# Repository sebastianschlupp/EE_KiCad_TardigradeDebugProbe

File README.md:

# Revision 0.1

## Hardware Design Description

## Test Results

✅ Voltage outputs OK: VUSB and 1V8

✅ SWD interface OK: connected and successfully erased using J-Link Segger and J-Flash Lite

✅ LEDs OK: VBUS; DBG_LED0; DBG_LED1; VCC; TGT_RESET (remark TGT_RESET led is on when reset is high so inactive ... might want to consider inverting LED in the future)

❌ USB interface not working at 1.8V: please see SAMD21 datasheet chapter 37.15: "The operating voltages must be 3.3V (Min. 3.0V, Max. 3.6V)."

✅ USB interface working at 3.3V

✅ Flashing using west and pyOCD working

## Planned Design Changes

- Replace LT1962-1.8 with a 3.3V regulator. Also look for a cheaper option since the LT part is around 5€
- Check BOM and investigate need for alternatives (optimise for availability and price)

---

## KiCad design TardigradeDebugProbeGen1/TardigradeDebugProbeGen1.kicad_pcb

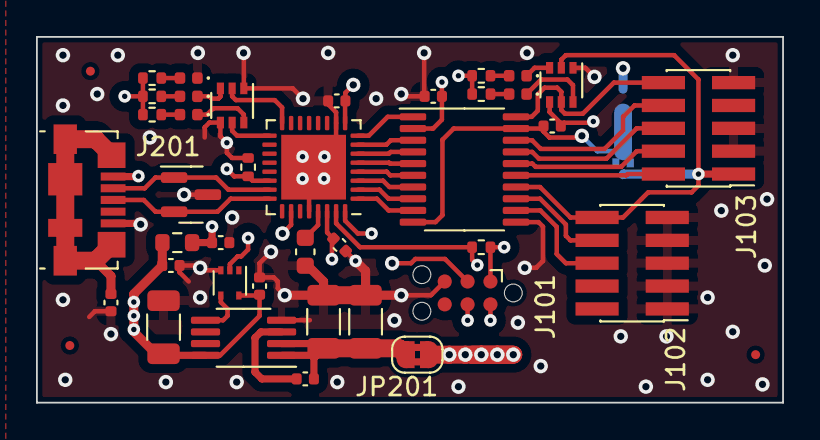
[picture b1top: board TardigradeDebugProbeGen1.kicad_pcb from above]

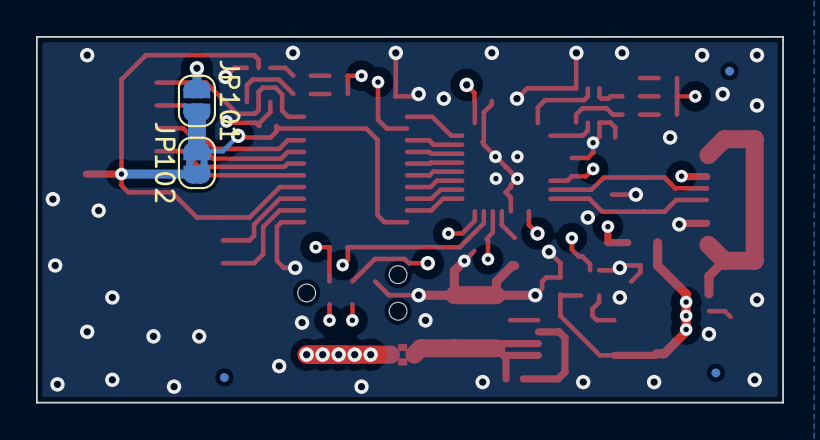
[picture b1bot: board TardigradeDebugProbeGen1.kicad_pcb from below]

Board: 6 copper layers, 41.5 x 20.3 mm, 46 parts (5 on the bottom side), 43 nets.

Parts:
C101, C102, C104, C105, C202, C203, C204: 100nF; C_0402_1005Metric
C103: 1uF; C_0603_1608Metric
C201: 4.7nF; C_0402_1005Metric
C205, C207, C208: 10uF; C_1206_3216Metric
C206: 10nF; C_0402_1005Metric
D101, D102: YELLOW; LED_0402_1005Metric
D103: RED; LED_0402_1005Metric
D104: GREEN; LED_0402_1005Metric
D201: LED; LED_0402_1005Metric
D202: SP0502BAHT; SOT-23
FB201: FerriteBead; R_0603_1608Metric
FID1, FID2, FID3, FID4, FID5, FID6: Fiducial; Fiducial_0.5mm_Mask1mm
J101: Conn_ARM_SWD_TagConnect_TC2030-NL; Tag-Connect_TC2030-IDC-NL_2x03_P1.27mm_Vertical
J102: Conn_02x05_Odd_Even; PinHeader_2x05_P1.27mm_Vertical_SMD
J103: Conn_ARM_JTAG_SWD_10; PinHeader_2x05_P1.27mm_Vertical_SMD
J201: USB_B_Micro; USB_Micro-B_Molex_47346-0001
JP101: SolderJumper_2_Open; SolderJumper-2_P1.3mm_Open_RoundedPad1.0x1.5mm
JP102, JP201: SolderJumper_2_Bridged; SolderJumper-2_P1.3mm_Bridged2Bar_RoundedPad1.0x1.5mm
Q101, Q102: ADC114; SOT-363_SC-70-6
R101, R102: 1k; R_0402_1005Metric
R103, R104, R105: 150; R_0402_1005Metric
R106, R201: 470; R_0402_1005Metric
U101: ATSAMD21E18A-M; QFN-32-1EP_5x5mm_P0.5mm_EP3.6x3.6mm
U102: TXS0108EPW; TSSOP-20_4.4x6.5mm_P0.65mm
U202: SN74LVC1G14DRL; SOT-553
U203: LT1962-1.8; MSOP-8_3x3mm_P0.65mm

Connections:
+1V8: C101.1, C102.1, C104.1, J101.1 (VCC), JP101.1 (A), JP201.2 (B), R101.2, U101.9 (VDDANA), U101.30 (VDDIN), U102.2 (VCCA)
/DBG_LED0: Q101.2 (B1), U101.16 (PA15)
/DBG_LED1: Q101.5 (B2), U101.17 (PA16)
/DBG_UART_RXD: J102.8, U102.13 (B7)
/DBG_UART_TXD: J102.6, U102.12 (B8)
/MCU_HARAKIRI: R102.2, U101.22 (PA23), U202.2
/SERCOM0_PAD1_SWO: U101.6 (PA05), U102.4 (A3)
/SERCOM1_PAD0_UART_TXD: U101.1 (PA00), U102.9 (A8)
/SERCOM1_PAD1_UART_RXD: U101.2 (PA01), U102.8 (A7)
/USB/USB_D+: D202.2 (K), J201.3 (D+), U101.24 (PA25)
/USB/USB_D-: D202.1 (K), J201.2 (D-), U101.23 (PA24)
GNDREF: C101.2, C102.2, C103.2, C104.2, C105.2, C201.1, C202.2, C203.2, C204.2, C205.2, C207.2, C208.2, D201.1 (K), D202.3 (A), J101.5 (GND), J102.1, J102.3, J102.5, J102.7, J102.9, J103.3 (GND), J103.5 (GND), J103.9 (GNDDetect), J201.5 (GND), Q101.1 (E1), Q101.4 (E2), Q102.1 (E1), Q102.4 (E2), R102.1, U101.10 (GND), U101.28 (GND), U101.33 (EP), U102.11 (GND), U202.3 (GND), U203.4 (GND)
unnamed: D101.2 (A), R103.1
unnamed: D101.1 (K), Q101.6 (C1)
unnamed: D102.2 (A), R104.1
unnamed: D102.1 (K), Q101.3 (C2)
unnamed: D103.2 (A), R105.1
unnamed: D103.1 (K), Q102.3 (C2)
unnamed: D104.2 (A), R106.1
unnamed: D104.1 (K), Q102.6 (C1)
unnamed: D201.2 (A), R201.1
unnamed: J101.4 (SWCLK), R101.1, U101.31 (PA30)
unnamed: J101.2 (SWDIO), U101.32 (PA31)
unnamed: J101.3 (~RESET), U101.26 (~RESET)
unnamed: J103.8 (NC/TDI), U102.18 (B2)
unnamed: J103.4 (SWDCLK/TCK), U102.16 (B4)
unnamed: J103.2 (SWDIO/TMS), U102.15 (B5)
unnamed: J103.6 (SWO/TDO), U102.17 (B3)
unnamed: C201.2, J201.6 (Shield)
unnamed: C203.1, FB201.1, J201.1 (VBUS)
unnamed: C105.1, JP101.2 (B), JP102.2 (B), U102.10 (OE), U102.19 (VCCB)
unnamed: C206.2, C207.1, C208.1, JP201.1 (A), U203.1 (OUT), U203.2 (SENSE)
unnamed: U101.3 (PA02), U102.7 (A6)
unnamed: U101.4 (PA03), U102.6 (A5)
unnamed: U101.5 (PA04), U102.5 (A4)
unnamed: U101.7 (PA06), U102.3 (A2)
unnamed: U101.8 (PA07), U102.1 (A1)
unnamed: C103.1, U101.29 (VDDCORE)
unnamed: C206.1, U203.3 (BYP)
unnamed: U202.4, U203.5 (~SHDN)
TGT_~RST: J103.10 (~RESET), Q102.5 (B2), U102.20 (B1)
VBUS: C202.1, C204.1, C205.1, FB201.2, R103.2, R104.2, R105.2, R106.2, R201.2, U202.5 (VCC), U203.8 (IN)
VCC: J102.10, J103.1 (VTref), JP102.1 (A), Q102.2 (B1), U102.14 (B6)

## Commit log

2023-11-07 Initial version. Ordered from Aisler
2024-01-25 Update and rename README.md to README.rst
    Made the readme file a restructured text instead of markdown file.
    Added user guide and required hand modifications for hardware revision 0.1
2024-02-12 Update .gitignore
    removed
    fp-lib-table
2024-03-26 Update README.rst
    formatting changes
2024-04-30 Update README.rst
    Removed User Guide (ported to Confluence)
